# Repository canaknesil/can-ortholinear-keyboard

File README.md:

# Can Ortholinear Keyboard

THIS PROJECT HAS NOT BEEN COMPLETED !!!

Ortholinear keyboard design.

Includes, 
- PCB design
- Plate design
- Case design
- Software (including firmware)

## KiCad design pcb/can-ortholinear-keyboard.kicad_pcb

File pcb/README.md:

# Can Ortholinear Keyboard PCB

CAD software: KiCad 5.1

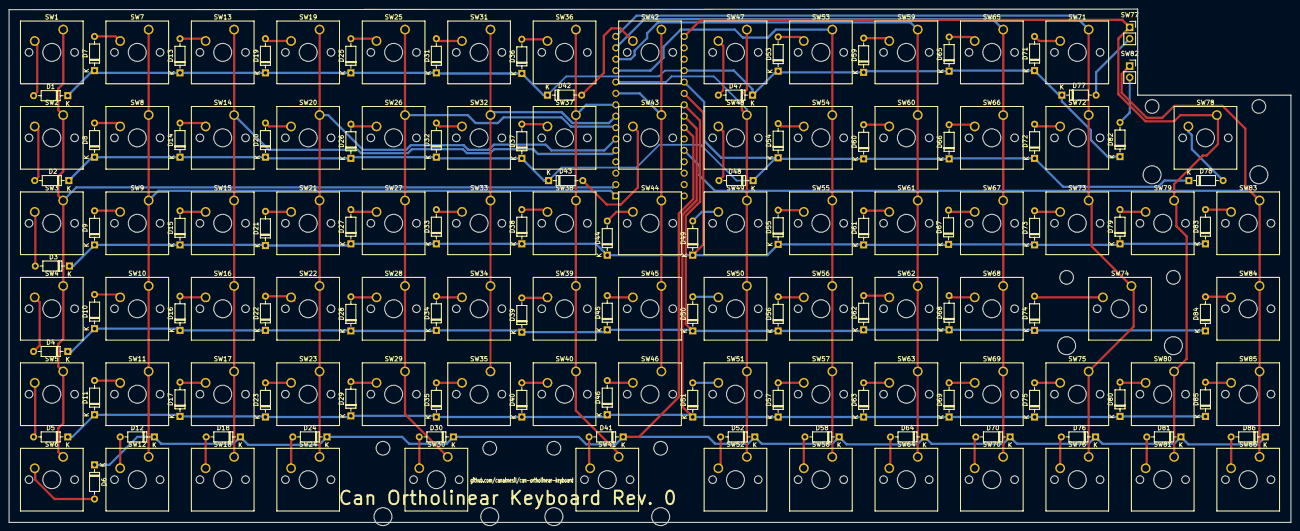
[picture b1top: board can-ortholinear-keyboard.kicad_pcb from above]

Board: 2 copper layers, 285.8 x 114.4 mm, 173 parts (1 on the bottom side), 107 nets.

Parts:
A1: Arduino_Nano_v3.x; Arduino_Nano
D1, D2, D3, D4, D5, D6, D7, D8, D9, D10, D11, D12, D13, D14, D15, D16, D17, D18, D19, D20, D21, D22, D23, D24, D25, D26, D27, D28, D29, D30, D31, D32, D33, D34, D35, D36, D37, D38, D39, D40, D41, D42, D43, D44, D45, D46, D47, D48, D49, D50, D51, D52, D53, D54, D55, D56, D57, D58, D59, D60, D61, D62, D63, D64, D65, D66, D67, D68, D69, D70, D71, D72, D73, D74, D75, D76, D77, D78, D79, D80, D81, D82, D83, D84, D85, D86: 1N4148; D_DO-35_SOD27_P7.62mm_Horizontal
SW1, SW2, SW3, SW4, SW5, SW6, SW7, SW8, SW9, SW10, SW11, SW12, SW13, SW14, SW15, SW16, SW17, SW18, SW19, SW20, SW21, SW22, SW23, SW24, SW25, SW26, SW27, SW28, SW29, SW31, SW32, SW33, SW34, SW35, SW36, SW37, SW38, SW39, SW40, SW42, SW43, SW44, SW45, SW46, SW47, SW48, SW49, SW50, SW51, SW52, SW53, SW54, SW55, SW56, SW57, SW58, SW59, SW60, SW61, SW62, SW63, SW64, SW65, SW66, SW67, SW68, SW69, SW70, SW71, SW72, SW73, SW75, SW76, SW79, SW80, SW81, SW83, SW84, SW85, SW86: SW_Push; SW_Cherry_MX_1.00u_PCB
SW30, SW41, SW74, SW78: SW_Push; SW_Cherry_MX_2.00u_PCB
SW77, SW82: SW_SPST; PinSocket_1x02_P2.54mm_Vertical

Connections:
/Col0: A1.2, SW1.1, SW2.1, SW3.1, SW4.1, SW5.1, SW6.1
/Col1: A1.1, SW7.1, SW8.1, SW9.1, SW10.1, SW11.1, SW12.1
/Col2: A1.5, SW13.1, SW14.1, SW15.1, SW16.1, SW17.1, SW18.1
/Col3: A1.6, SW19.1, SW20.1, SW21.1, SW22.1, SW23.1, SW24.1
/Col4: A1.7, SW25.1, SW26.1, SW27.1, SW28.1, SW29.1, SW30.1
/Col5: A1.8, SW31.1, SW32.1, SW33.1, SW34.1, SW35.1
/Col6: A1.9, SW36.1, SW37.1, SW38.1, SW39.1, SW40.1, SW41.1
/Col7: A1.10, SW42.1, SW43.1, SW44.1, SW45.1, SW46.1
/Col8: A1.11, SW47.1, SW48.1, SW49.1, SW50.1, SW51.1, SW52.1
/Col9: A1.12, SW53.1, SW54.1, SW55.1, SW56.1, SW57.1, SW58.1
/Col10: A1.13, SW59.1, SW60.1, SW61.1, SW62.1, SW63.1, SW64.1
/Col11: A1.14, SW65.1, SW66.1, SW67.1, SW68.1, SW69.1, SW70.1
/Col12: A1.15, SW71.1, SW72.1, SW73.1, SW74.1, SW75.1, SW76.1
/Col13: A1.16, SW77.1, SW78.1, SW79.1, SW80.1, SW81.1
/Col14: A1.26, SW82.1, SW83.1, SW84.1, SW85.1, SW86.1
/Row0: A1.19, D1.1, D7.1, D13.1, D19.1, D25.1, D31.1, D36.1, D42.1, D47.1, D53.1, D59.1, D65.1, D71.1, D77.1, D82.1
/Row1: A1.20, D2.1, D8.1, D14.1, D20.1, D26.1, D32.1, D37.1, D43.1, D48.1, D54.1, D60.1, D66.1, D72.1, D78.1
/Row2: A1.21, D3.1, D9.1, D15.1, D21.1, D27.1, D33.1, D38.1, D44.1, D49.1, D55.1, D61.1, D67.1, D73.1, D79.1, D83.1
/Row3: A1.22, D4.1, D10.1, D16.1, D22.1, D28.1, D34.1, D39.1, D45.1, D50.1, D56.1, D62.1, D68.1, D74.1, D84.1
/Row4: A1.23, D5.1, D11.1, D17.1, D23.1, D29.1, D35.1, D40.1, D46.1, D51.1, D57.1, D63.1, D69.1, D75.1, D80.1, D85.1
/Row5: A1.24, D6.1, D12.1, D18.1, D24.1, D30.1, D41.1, D52.1, D58.1, D64.1, D70.1, D76.1, D81.1, D86.1
unnamed: D1.2, SW1.2
unnamed: D2.2, SW2.2
unnamed: D3.2, SW3.2
unnamed: D4.2, SW4.2
unnamed: D5.2, SW5.2
unnamed: D6.2, SW6.2
unnamed: D7.2, SW7.2
unnamed: D8.2, SW8.2
unnamed: D9.2, SW9.2
unnamed: D10.2, SW10.2
unnamed: D11.2, SW11.2
unnamed: D12.2, SW12.2
unnamed: D13.2, SW13.2
unnamed: D14.2, SW14.2
unnamed: D15.2, SW15.2
unnamed: D16.2, SW16.2
unnamed: D17.2, SW17.2
unnamed: D18.2, SW18.2
unnamed: D19.2, SW19.2
unnamed: D20.2, SW20.2
unnamed: D21.2, SW21.2
unnamed: D22.2, SW22.2
unnamed: D23.2, SW23.2
unnamed: D24.2, SW24.2
unnamed: D25.2, SW25.2
unnamed: D26.2, SW26.2
unnamed: D27.2, SW27.2
unnamed: D28.2, SW28.2
unnamed: D29.2, SW29.2
unnamed: D30.2, SW30.2
unnamed: D31.2, SW31.2
unnamed: D32.2, SW32.2
unnamed: D33.2, SW33.2
unnamed: D34.2, SW34.2
unnamed: D35.2, SW35.2
unnamed: D36.2, SW36.2
unnamed: D37.2, SW37.2
unnamed: D38.2, SW38.2
unnamed: D39.2, SW39.2
unnamed: D40.2, SW40.2
unnamed: D41.2, SW41.2
unnamed: D42.2, SW42.2
unnamed: D43.2, SW43.2
unnamed: D44.2, SW44.2
unnamed: D45.2, SW45.2
unnamed: D46.2, SW46.2
unnamed: D47.2, SW47.2
unnamed: D48.2, SW48.2
unnamed: D49.2, SW49.2
unnamed: D50.2, SW50.2
unnamed: D51.2, SW51.2
unnamed: D52.2, SW52.2
unnamed: D53.2, SW53.2
unnamed: D54.2, SW54.2
unnamed: D55.2, SW55.2
unnamed: D56.2, SW56.2
unnamed: D57.2, SW57.2
unnamed: D58.2, SW58.2
unnamed: D59.2, SW59.2
unnamed: D60.2, SW60.2
unnamed: D61.2, SW61.2
unnamed: D62.2, SW62.2
unnamed: D63.2, SW63.2
unnamed: D64.2, SW64.2
unnamed: D65.2, SW65.2
unnamed: D66.2, SW66.2
unnamed: D67.2, SW67.2
unnamed: D68.2, SW68.2
unnamed: D69.2, SW69.2
unnamed: D70.2, SW70.2
unnamed: D71.2, SW71.2
unnamed: D72.2, SW72.2
unnamed: D73.2, SW73.2
unnamed: D74.2, SW74.2
unnamed: D75.2, SW75.2
unnamed: D76.2, SW76.2
unnamed: D77.2, SW77.2
unnamed: D78.2, SW78.2
unnamed: D79.2, SW79.2
unnamed: D80.2, SW80.2
unnamed: D81.2, SW81.2
unnamed: D82.2, SW82.2
unnamed: D83.2, SW83.2
unnamed: D84.2, SW84.2
unnamed: D85.2, SW85.2
unnamed: D86.2, SW86.2

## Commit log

2020-07-02 Schematics without footprints.
2020-07-02 Assign footprints except 2 toggle switches.
2020-07-03 Placed every component on PCB.
2020-07-03 Drew all the tracks.
2020-07-04 Silkscreen modifications.
2020-07-05 Rerouted with thicker tracks.
2020-07-14 Removed the gap between switches and rerouted.
2020-07-14 Generated gerber and drill files acc. to the Kicad 5.1 tutorial at JLCPCB.
2020-07-30 Added plate design.
2020-07-30 Added software.
2020-07-30 Created holes for toggle switches.
2020-07-30 Fixed readme links.
2020-08-01 Started case design.
2020-08-02 Finalized case design.
2020-08-02 Added pcb to the 3d case model.
2020-08-03 Fixed size and orientation of toggle switch holes.
2020-08-03 Prepare for 3d printing + minor modifications.
2020-08-12 Better coding, software submodule update
2021-01-26 printing in 2 pieces without reversing inclination and centering
2024-07-03 schematic and layout for v0.1
